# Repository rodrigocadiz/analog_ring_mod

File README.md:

# Analog ring modulation: a DIY approach inspired by historical techniques

## Overview

We present a device that implements a ring modulator intended to recreate historical analog audio. As simple as it sounds, the multiplication of two analog audio signals is not a straightforward task, mainly due to phenomena such as saturation or non-linearity. Drawing inspiration from historical realizations of ring modulation, we experimented with the most common methods described in the literature. Our device, which is comparatively inexpensive, improves upon the aforementioned alternatives from a DIY perspective. It is predominantly analog, adhering to the practices of the first decades of electroacoustic music, with the notable exception of the digital control for the sinusoidal carrier. We aim to strike a balance between analog audio technology and modern components and techniques. Additionally, this paper includes audio-visual demonstrations that showcase the practical uses of our ring modulator. A comprehensive GitHub repository provides open access to all the resources required for DIY enthusiasts to replicate our implementation.

## Authors
Tomas Koljatic, Michel Rozas, Cristián Garcés, Juan Parra Cancino, Rodrigo F. Cádiz

Pontificia Universidad Católica de Chile

Orpheus Instituut

## Demo videos 
Video 1:

Video 2: 

## Software Installation

The software for the Ring Modulator project is developed to be used with PlatformIO, an open source ecosystem for IoT development. To get started with PlatformIO, you can follow the installation guide here:

- [PlatformIO Installation Guide](https://docs.platformio.org/en/latest/core/installation.html)

Once PlatformIO is installed, you can clone this repository and open the firmware folder project within PlatformIO IDE.

## Hardware Design

The hardware for the Ring Modulator is developed using Autodesk Eagle. This provides a robust framework for designing printed circuit boards (PCBs) that are crucial for our project. You can find the hardware design files in the `hardware` directory of this repository.

For those new to Autodesk Eagle, you can learn more and get started with your designs here:

- [Autodesk Eagle](https://www.autodesk.com/products/eagle/overview)

## Acknowledgments/Contributing

The authors would like to thank Stockahusen Stiftung fur Musik for their support; María Julia Mancero for her participation as a piano performer in the videos; and the anonymous reviewers for their insightful comments and suggestions. This project was funded by the Office for the Arts and Culture of the Vice Presidency for Research, Pontificia Universidad Católica de Chile (ArTeCiH grant) and by ANID/Fondecyt 1230926 and ANID/Anillo ATE220041.

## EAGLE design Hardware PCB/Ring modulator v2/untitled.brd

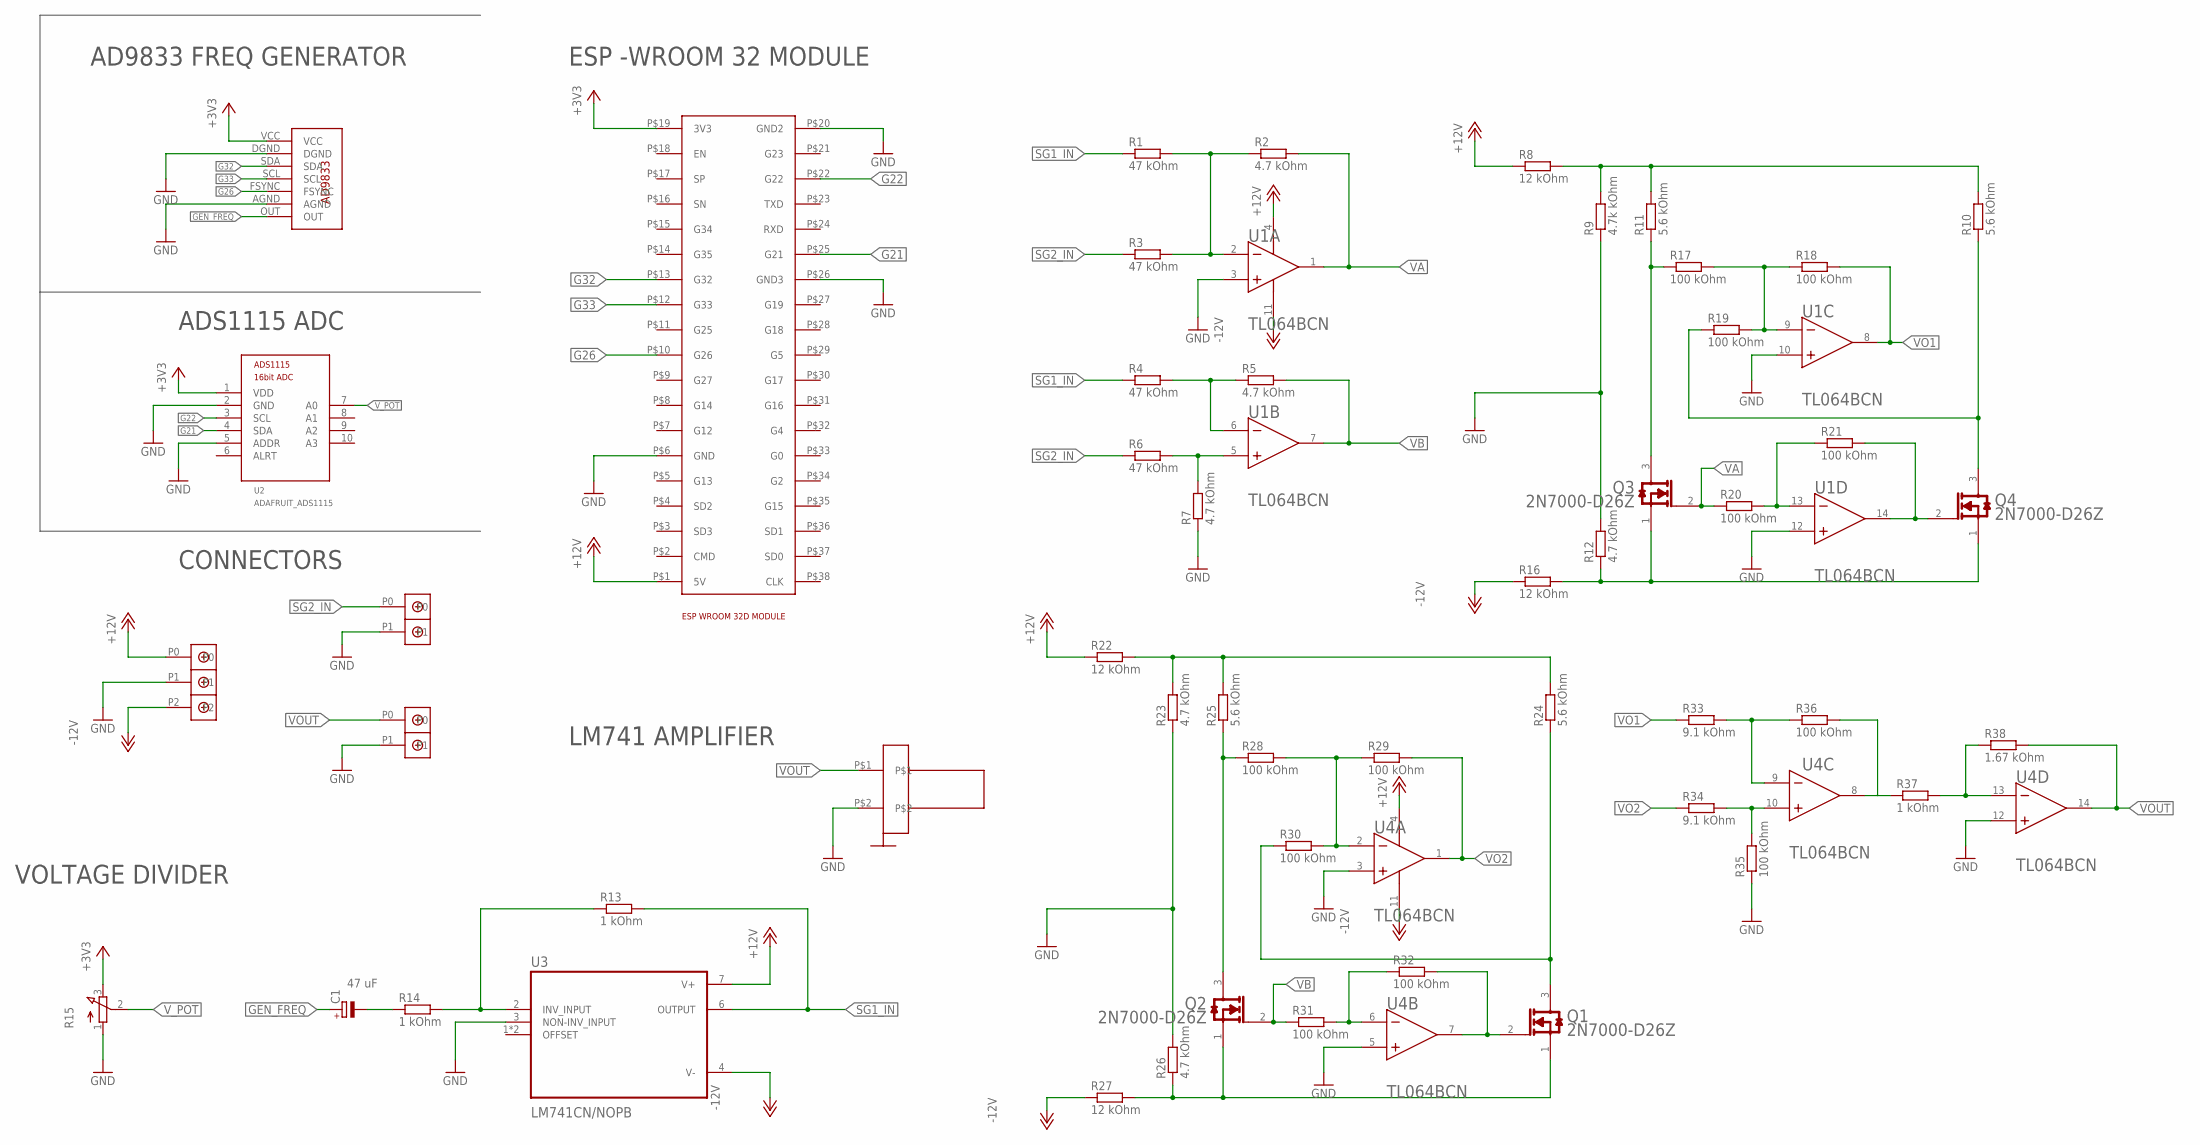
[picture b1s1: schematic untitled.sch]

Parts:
C1: 47 uF; E1,8-4
Q1, Q2, Q3, Q4: ON_SEMICONDUCTOR_2N7000-D26ZON_SEMICONDUCTOR_2N70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; ON_SEMICONDUCTOR_2N7000-D26Z_0
R1, R3, R4, R6: 47 kOhm; 0204/7
R2, R5, R7, R12, R23, R26: 4.7 kOhm; 0204/7
R8, R16, R22, R27: 12 kOhm; 0204/7
R9: 4.7k kOhm; 0204/7
R10, R11, R24, R25: 5.6 kOhm; 0204/7
R13, R14, R37: 1 kOhm; 0204/7
R15: 3RP/1610N
R17, R18, R19, R20, R21, R28, R29, R30, R31, R32, R35, R36: 100 kOhm; 0204/7
R33, R34: 9.1 kOhm; 0204/7
R38: 1.67 kOhm; 0204/7
U1, U4: TEXAS_INSTRUMENTS_TL064BCNTEXAS_INSTRUMENTS_TL064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; TEXAS_INSTRUMENTS_TL064BCN_0
U2: ADAFRUIT_ADS1115; ADAFRUIT_ADS1115_16BIT_I2C_ADC
U3: LM741CN/NOPB; DIP794W45P254L959H508Q8
U$1: ESP32
U$2: A9833; AD9833
U$3, U$5: DBCONN-1X2
U$4: DBCONN-1X3
U$6: FP

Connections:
+3V3: R15.3 (E), U2.1 (VDD), U$1.P$19 (3V3), U$2.VCC
+12V: R8.1, R22.1, U1.4 (VCC+), U3.7 (V+), U4.4 (VCC+), U$1.P$1 (5V), U$4.P0
-12V: R16.1, R27.1, U1.11 (VCC-), U3.4 (V-), U4.11 (VCC-), U$4.P2
G21: U2.4 (SDA), U$1.P$25 (G21)
G22: U2.3 (SCL), U$1.P$22 (G22)
G26: U$1.P$10 (G26), U$2.FSYNC
G32: U$1.P$13 (G32), U$2.SDA
G33: U$1.P$12 (G33), U$2.SCL
GEN_FREQ: C1.+, U$2.OUT
GND: R7.1, R9.1, R12.2, R15.1 (A), R23.1, R26.2, R35.1, U1.3 (IN1+), U1.10 (IN3+), U1.12 (IN4+), U2.2 (GND), U2.5 (ADDR), U3.3 (NON-INV_INPUT), U4.3 (IN1+), U4.5 (IN2+), U4.12 (IN4+), U$1.P$6 (GND), U$1.P$20 (GND2), U$1.P$26 (GND3), U$2.AGND, U$2.DGND, U$3.P1, U$4.P1, U$5.P1, U$6.P$2
unnamed: R1.2, R2.1, R3.2, U1.2 (IN1-)
unnamed: R4.2, R5.1, U1.6 (IN2-)
unnamed: R8.2, R9.2, R10.2, R11.2
unnamed: R13.1, R14.2, U3.2 (INV_INPUT)
unnamed: C1.-, R14.1
unnamed: R6.2, R7.2, U1.5 (IN2+)
unnamed: Q3.3 (D), R11.1, R17.1
unnamed: Q3.1 (S), Q4.1 (S), R12.1, R16.2
unnamed: Q4.3 (D), R10.1, R19.1
unnamed: R37.2, R38.1, U4.13 (IN4-)
unnamed: R20.2, R21.1, U1.13 (IN4-)
unnamed: R17.2, R18.1, R19.2, U1.9 (IN3-)
unnamed: Q4.2 (G), R21.2, U1.14 (OUT4)
unnamed: R22.2, R23.2, R24.2, R25.2
unnamed: Q1.1 (S), Q2.1 (S), R26.1, R27.2
unnamed: Q2.3 (D), R25.1, R28.1
unnamed: Q1.3 (D), R24.1, R30.1
unnamed: R28.2, R29.1, R30.2, U4.2 (IN1-)
unnamed: R33.2, R36.1, U4.9 (IN3-)
unnamed: R31.2, R32.1, U4.6 (IN2-)
unnamed: Q1.2 (G), R32.2, U4.7 (OUT2)
unnamed: R36.2, R37.1, U4.8 (OUT3)
unnamed: R34.2, R35.2, U4.10 (IN3+)
SG1_IN: R1.1, R4.1, R13.2, U3.6 (OUTPUT)
SG2_IN: R3.1, R6.1, U$3.P0
VA: Q3.2 (G), R2.2, R20.1, U1.1 (OUT1)
VB: Q2.2 (G), R5.2, R31.1, U1.7 (OUT2)
VO1: R18.2, R33.1, U1.8 (OUT3)
VO2: R29.2, R34.1, U4.1 (OUT1)
VOUT: R38.2, U4.14 (OUT4), U$5.P0, U$6.P$1
V_POT: R15.2 (S), U2.7 (A0)

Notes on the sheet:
ESP -WROOM 32 MODULE
AD9833 FREQ GENERATOR
ADS1115 ADC
CONNECTORS
LM741 AMPLIFIER
VOLTAGE DIVIDER

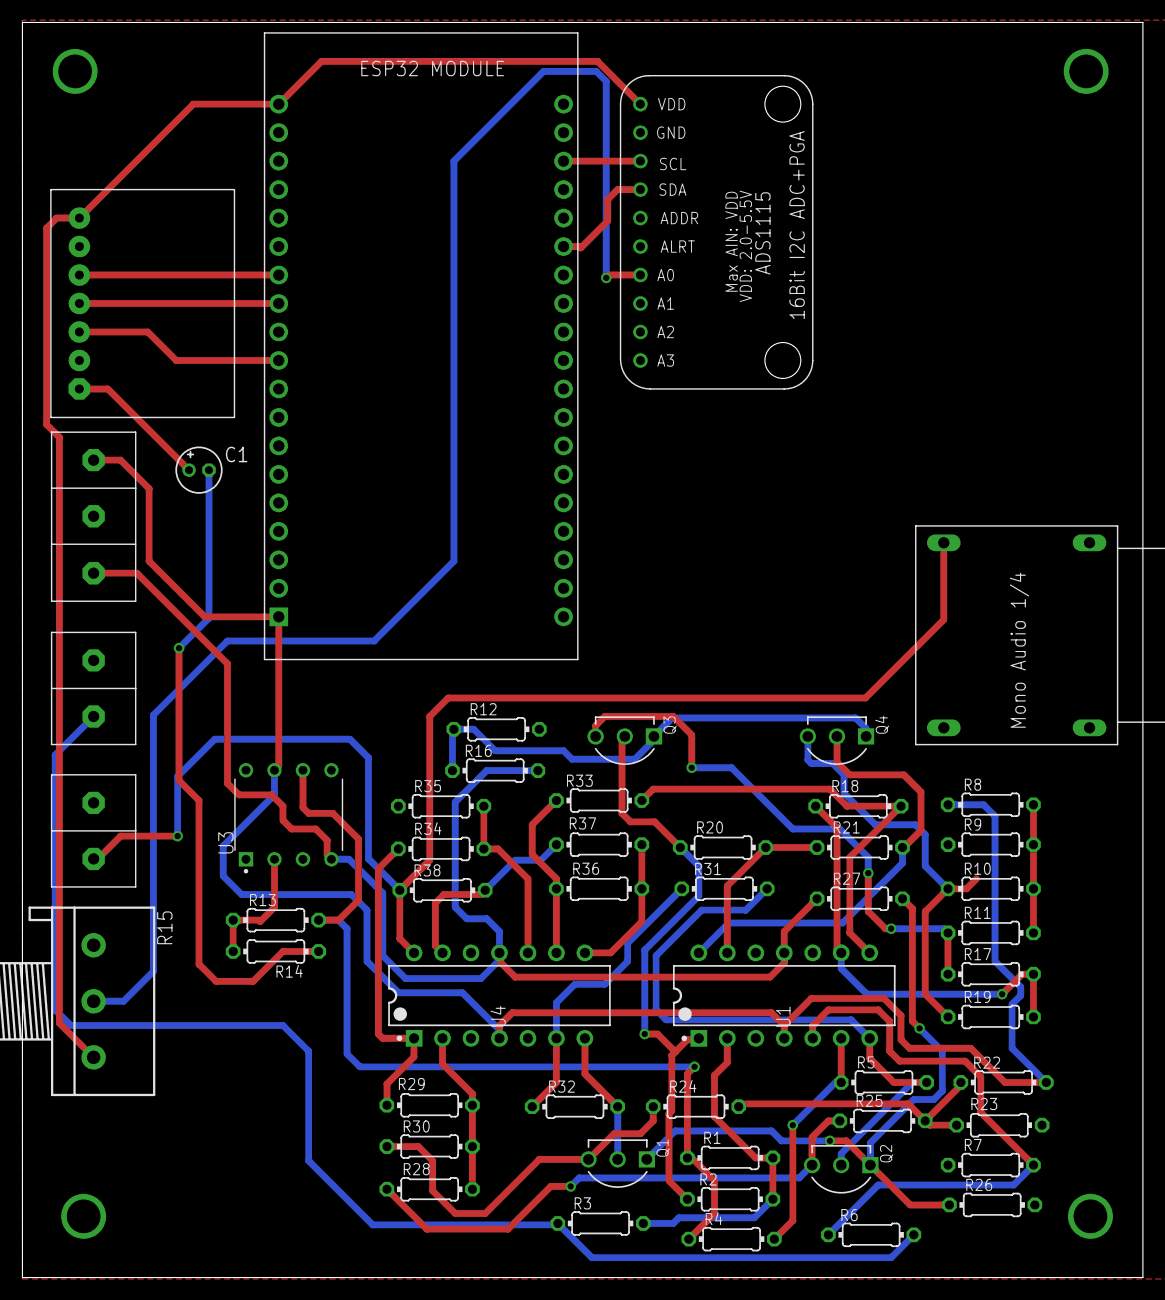
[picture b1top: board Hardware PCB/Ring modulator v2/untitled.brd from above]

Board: 2 copper layers, 99.9 x 111.9 mm, 53 parts (0 on the bottom side), 41 nets.

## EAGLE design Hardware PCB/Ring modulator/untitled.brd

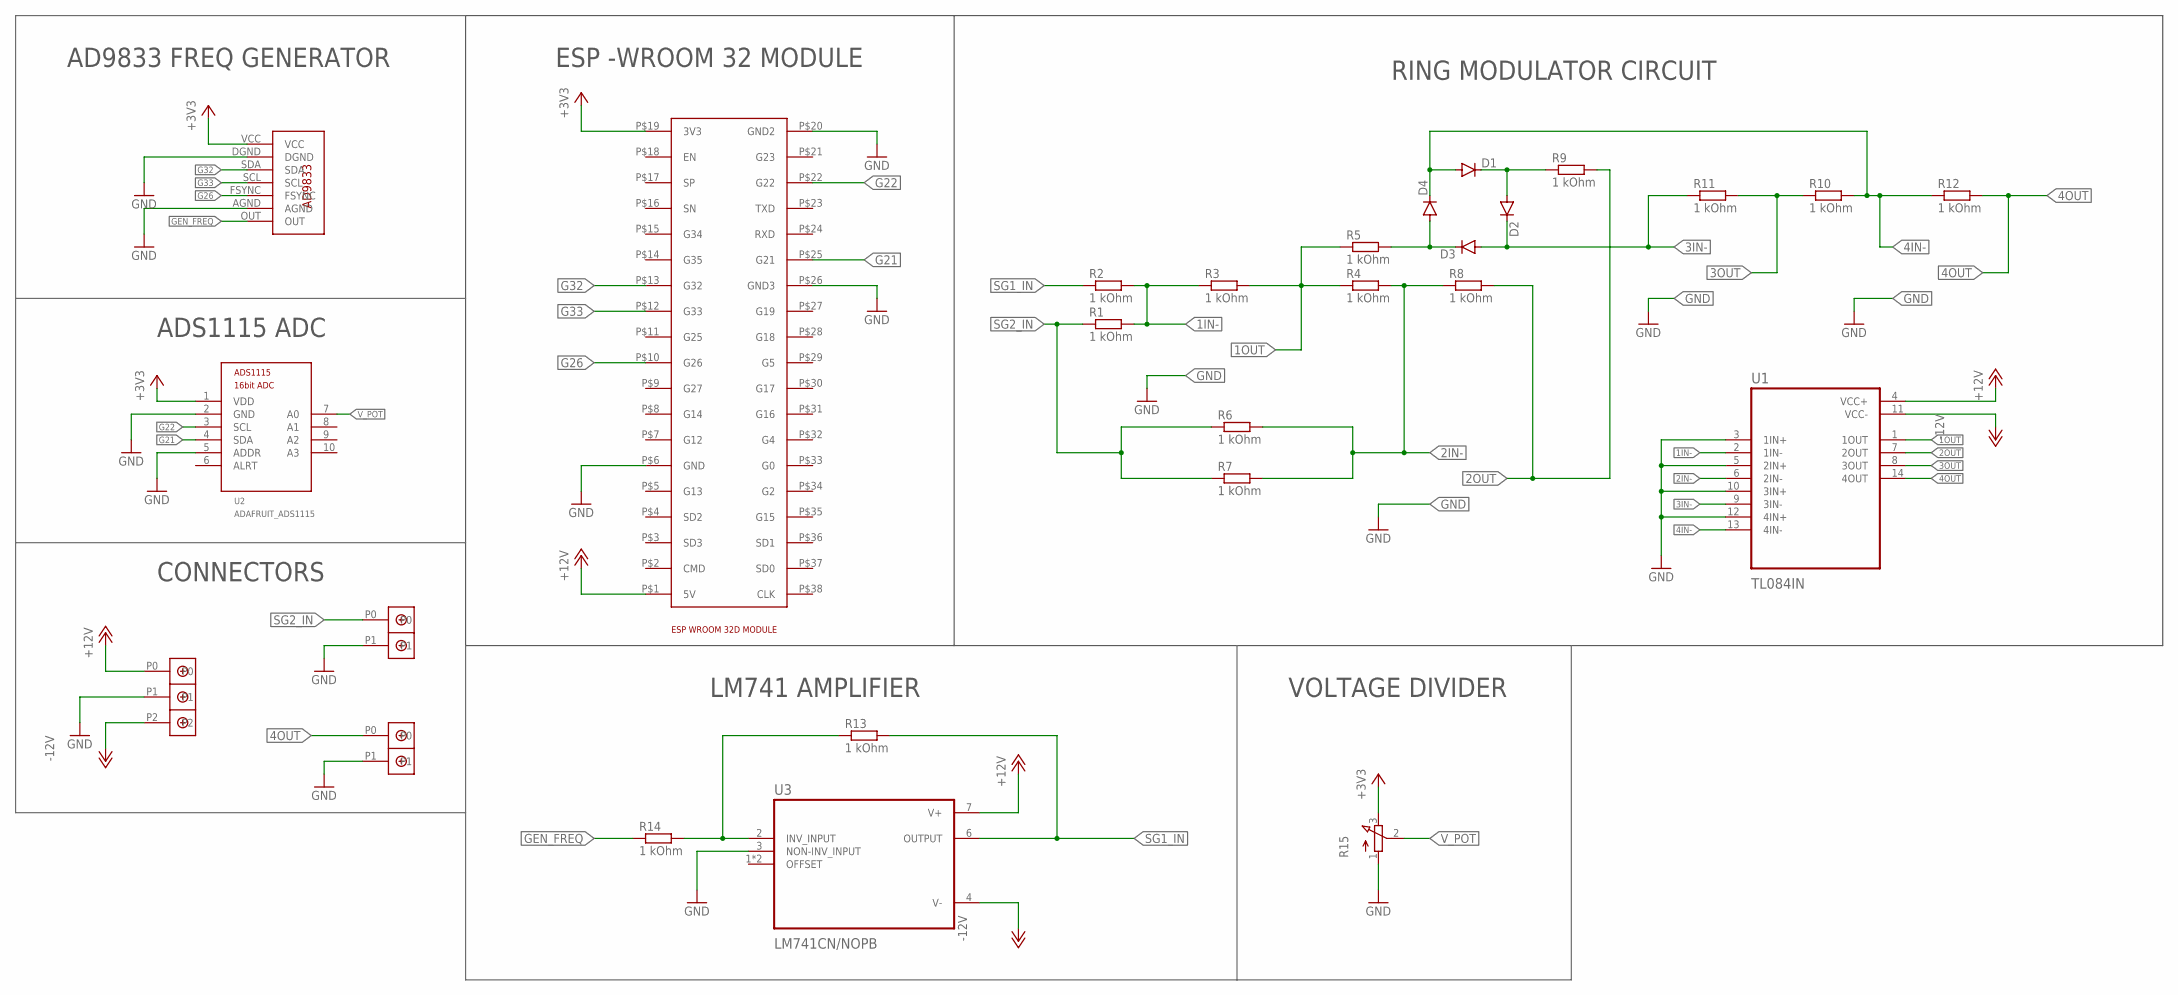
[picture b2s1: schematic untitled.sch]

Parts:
D1, D2, D3, D4: 1N4148DO35-7; DO35-7
R1, R2, R3, R4, R5, R6, R7, R8, R9, R10, R11, R12, R13, R14: 1 kOhm; 0204/7
R15: 3RP/1610N
U1: TL084IN; DIP794W45P254L1969H508Q14
U2: ADAFRUIT_ADS1115; ADAFRUIT_ADS1115_16BIT_I2C_ADC
U3: LM741CN/NOPB; DIP794W45P254L959H508Q8
U$1: ESP32
U$2: A9833; AD9833
U$3, U$5: DBCONN-1X2
U$4: DBCONN-1X3

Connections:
1IN-: R1.2, R2.2, R3.1, U1.2 (1IN-)
1OUT: R3.2, R4.1, R5.1, U1.1 (1OUT)
2IN-: R4.2, R6.2, R7.2, R8.1, U1.6 (2IN-)
2OUT: R8.2, R9.2, U1.7 (2OUT)
3IN-: D2.C, D3.A, R11.1, U1.9 (3IN-)
3OUT: R10.1, R11.2, U1.8 (3OUT)
4IN-: D1.A, D4.C, R10.2, R12.1, U1.13 (4IN-)
4OUT: R12.2, U1.14 (4OUT), U$5.P0
+3V3: R15.3 (E), U2.1 (VDD), U$1.P$19 (3V3), U$2.VCC
+12V: U1.4 (VCC+), U3.7 (V+), U$1.P$1 (5V), U$4.P0
-12V: U1.11 (VCC-), U3.4 (V-), U$4.P2
G21: U2.4 (SDA), U$1.P$25 (G21)
G22: U2.3 (SCL), U$1.P$22 (G22)
G26: U$1.P$10 (G26), U$2.FSYNC
G32: U$1.P$13 (G32), U$2.SDA
G33: U$1.P$12 (G33), U$2.SCL
GEN_FREQ: R14.1, U$2.OUT
GND: R15.1 (A), U1.3 (1IN+), U1.5 (2IN+), U1.10 (3IN+), U1.12 (4IN+), U2.2 (GND), U2.5 (ADDR), U3.3 (NON-INV_INPUT), U$1.P$6 (GND), U$1.P$20 (GND2), U$1.P$26 (GND3), U$2.AGND, U$2.DGND, U$3.P1, U$4.P1, U$5.P1
unnamed: D3.C, D4.A, R5.2
unnamed: D1.C, D2.A, R9.1
unnamed: R13.1, R14.2, U3.2 (INV_INPUT)
SG1_IN: R2.1, R13.2, U3.6 (OUTPUT)
SG2_IN: R1.1, R6.1, R7.1, U$3.P0
V_POT: R15.2 (S), U2.7 (A0)

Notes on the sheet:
RING MODULATOR CIRCUIT
ESP -WROOM 32 MODULE
AD9833 FREQ GENERATOR
ADS1115 ADC
CONNECTORS
LM741 AMPLIFIER
VOLTAGE DIVIDER

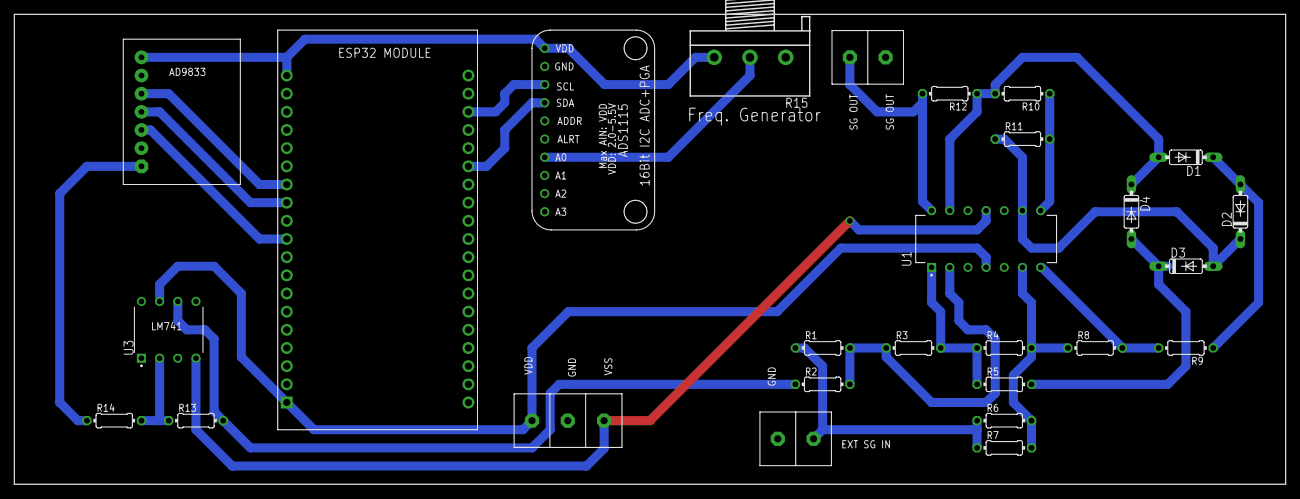
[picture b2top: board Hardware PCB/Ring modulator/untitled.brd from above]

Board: 2 copper layers, 177.8 x 65.7 mm, 27 parts (0 on the bottom side), 24 nets.

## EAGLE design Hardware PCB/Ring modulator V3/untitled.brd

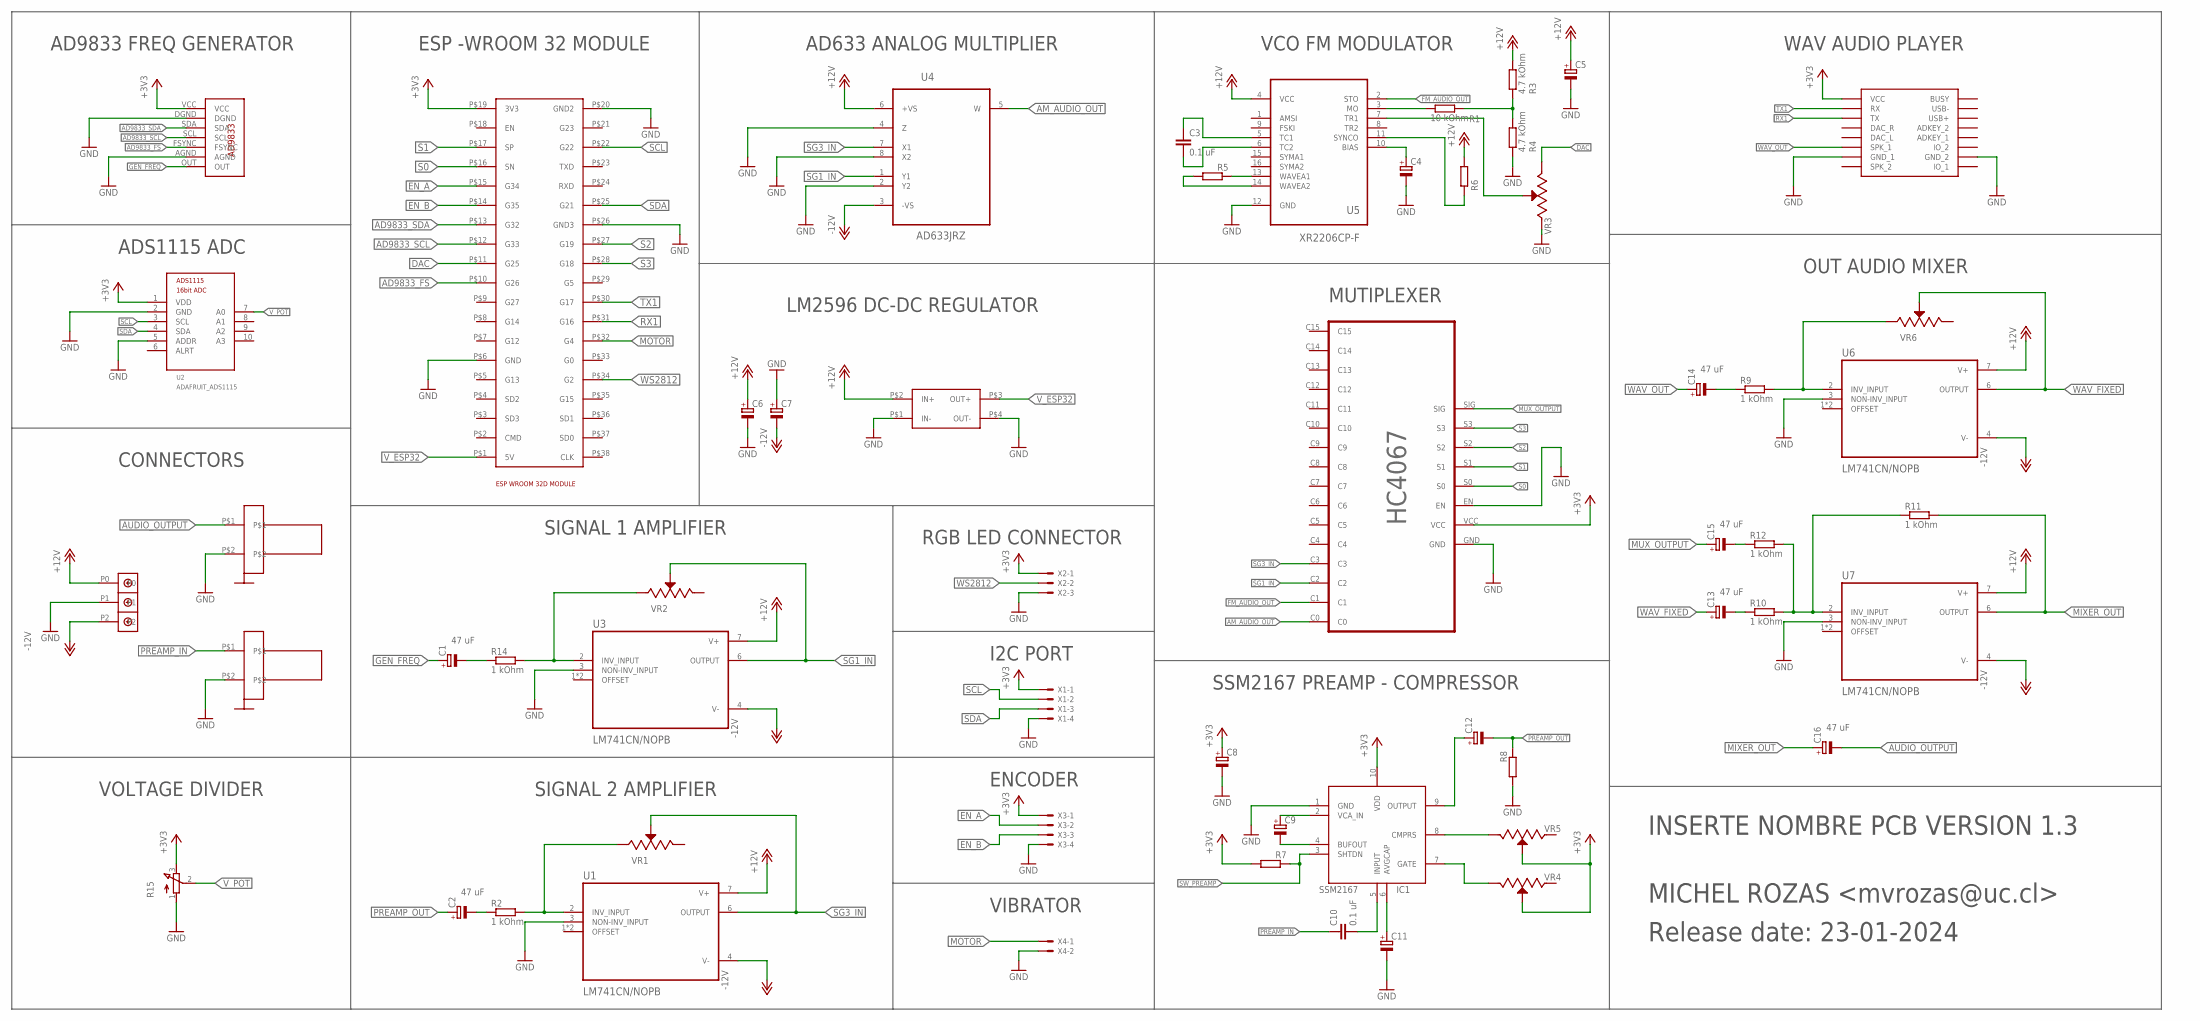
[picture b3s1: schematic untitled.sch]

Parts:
C1, C2, C13, C14, C15, C16: 47 uF; E1,8-4
C3, C10: 0.1 uF; C050-030X075
C4, C5: 1 uF; E1,8-4
C6, C7: 100 uF; E1,8-4
C8, C9, C11, C12: 10 uF; E1,8-4
IC1: SSM2167; MSOP10
R1, R6: 10 kOhm; 0204/7
R2, R9, R10, R11, R12, R14: 1 kOhm; 0204/7
R3, R4: 4.7 kOhm; 0204/7
R5: 200 Ohm; 0204/7
R7: 500 kOhm; 0204/7
R8: 100 kOhm; 0204/7
R15: 3RP/1610N
U1, U3, U6, U7: LM741CN/NOPB; DIP794W45P254L959H508Q8
U2: ADAFRUIT_ADS1115; ADAFRUIT_ADS1115_16BIT_I2C_ADC
U4: AD633JRZ; SOIC127P600X175-8N
U5: XR2206CP-F; DIP254P762X533-16
U$1: ESP32
U$2: A9833; AD9833
U$3: LM2596
U$4: DBCONN-1X3
U$5: HC4067_BREAKOUT_BOARD; ANALOG_MUX_BREAKOUT_HC4067
U$6, U$7: FP
U$8: DFPLAYER
VR1, VR2, VR3, VR4, VR5, VR6: 3296W-1-104LF; TRIM_3296W-1-104LF
X1, X3: JST-XH-04-PIN-ROUND-PAD; JST-XH-04-PACKAGE-ROUND-PAD
X2: JST-XH-03-PIN-ROUND-PAD; JST-XH-03-PACKAGE-ROUND-PAD
X4: JST-XH-02-PIN-ROUND-PAD; JST-XH-02-PACKAGE-ROUND-PAD

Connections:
+3V3: C8.+, IC1.10 (VDD), R7.1, R15.3 (E), U2.1 (VDD), U$1.P$19 (3V3), U$2.VCC, U$5.VCC, U$8.VCC, VR4.2 (WIPER), VR5.2 (WIPER), X1.1, X2.1, X3.1
+12V: C5.+, C6.+, R3.2, R6.2, U1.7 (V+), U3.7 (V+), U4.6 (+VS), U5.4 (VCC), U6.7 (V+), U7.7 (V+), U$3.P$2 (IN+), U$4.P0
-12V: C7.-, U1.4 (V-), U3.4 (V-), U4.3 (-VS), U6.4 (V-), U7.4 (V-), U$4.P2
AD9833_FS: U$1.P$10 (G26), U$2.FSYNC
AD9833_SCL: U$1.P$12 (G33), U$2.SCL
AD9833_SDA: U$1.P$13 (G32), U$2.SDA
AM_AUDIO_OUT: U4.5 (W), U$5.C0
AUDIO_OUTPUT: C16.-, U$6.P$1
DAC: U$1.P$11 (G25), VR3.3 (CW)
EN_A: U$1.P$15 (G34), X3.2
EN_B: U$1.P$14 (G35), X3.3
FM_AUDIO_OUT: U5.2 (STO), U$5.C1
GEN_FREQ: C1.+, U$2.OUT
GND: C4.-, C5.-, C6.-, C7.+, C8.-, C11.-, IC1.1 (GND), R4.1, R8.1, R15.1 (A), U1.3 (NON-INV_INPUT), U2.2 (GND), U2.5 (ADDR), U3.3 (NON-INV_INPUT), U4.2 (Y2), U4.4 (Z), U4.8 (X2), U5.12 (GND), U6.3 (NON-INV_INPUT), U7.3 (NON-INV_INPUT), U$1.P$6 (GND), U$1.P$20 (GND2), U$1.P$26 (GND3), U$2.AGND, U$2.DGND, U$3.P$1 (IN-), U$4.P1, U$5.EN, U$6.P$2, U$7.P$2, U$8.GND_1, U$8.GND_2, VR3.1 (CCW), X1.4, X2.3, X3.4, X4.2
MIXER_OUT: C16.+, R11.2, U7.6 (OUTPUT)
MOTOR: U$1.P$32 (G4), X4.1
MUX_OUTPUT: C15.+, U$5.SIG
unnamed: R2.2, U1.2 (INV_INPUT), VR1.1 (CCW)
unnamed: C2.-, R2.1
unnamed: R1.1, U5.3 (MO)
unnamed: R14.2, U3.2 (INV_INPUT), VR2.1 (CCW)
unnamed: C1.-, R14.1
unnamed: R1.2, R3.1, R4.2
unnamed: C3.1, U5.5 (TC1)
unnamed: C3.2, U5.6 (TC2)
unnamed: U5.7 (TR1), VR3.2 (WIPER)
unnamed: R5.2, U5.13 (WAVEA1)
unnamed: R5.1, U5.14 (WAVEA2)
unnamed: R6.1, U5.11 (SYNCO)
unnamed: C4.+, U5.10 (BIAS)
unnamed: C10.2, IC1.5 (INPUT)
unnamed: C9.+, IC1.2 (VCA_IN)
unnamed: C9.-, IC1.4 (BUFOUT)
unnamed: C11.+, IC1.6 (AVGCAP)
unnamed: IC1.8 (CMPRS), VR5.3 (CW)
unnamed: IC1.7 (GATE), VR4.3 (CW)
unnamed: C12.+, IC1.9 (OUTPUT)
unnamed: R9.2, U6.2 (INV_INPUT), VR6.1 (CCW)
unnamed: C14.-, R9.1
unnamed: R10.2, R11.1, R12.2, U7.2 (INV_INPUT)
unnamed: C13.-, R10.1
unnamed: C15.-, R12.1
PREAMP_IN: C10.1, U$7.P$1
PREAMP_OUT: C2.+, C12.-, R8.2
RX1: U$1.P$31 (G16), U$8.TX
S0: U$1.P$16 (SN), U$5.S0
S1: U$1.P$17 (SP), U$5.S1
S2: U$1.P$27 (G19), U$5.S2
S3: U$1.P$28 (G18), U$5.S3
SCL: U2.3 (SCL), U$1.P$22 (G22), X1.2
SDA: U2.4 (SDA), U$1.P$25 (G21), X1.3
SG1_IN: U3.6 (OUTPUT), U4.1 (Y1), U$5.C2, VR2.2 (WIPER)
SG3_IN: U1.6 (OUTPUT), U4.7 (X1), U$5.C3, VR1.2 (WIPER)
SW_PREAMP: IC1.3 (SHTDN), R7.2
TX1: U$1.P$30 (G17), U$8.RX
V_ESP32: U$1.P$1 (5V), U$3.P$3 (OUT+)
V_POT: R15.2 (S), U2.7 (A0)
WAV_FIXED: C13.+, U6.6 (OUTPUT), VR6.2 (WIPER)
WAV_OUT: C14.+, U$8.SPK1 (SPK_1)
WS2812: U$1.P$34 (G2), X2.2

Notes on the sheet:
ESP -WROOM 32 MODULE
AD9833 FREQ GENERATOR
ADS1115 ADC
CONNECTORS
SIGNAL 1 AMPLIFIER
VOLTAGE DIVIDER
SIGNAL 2 AMPLIFIER
AD633 ANALOG MULTIPLIER
LM2596 DC-DC REGULATOR
RGB LED CONNECTOR
I2C PORT
ENCODER
VIBRATOR
VCO FM MODULATOR
MUTIPLEXER
SSM2167 PREAMP - COMPRESSOR
WAV AUDIO PLAYER
OUT AUDIO MIXER
INSERTE NOMBRE PCB VERSION 1.3
MICHEL ROZAS <mvrozas@uc.cl>
Release date: 23-01-2024

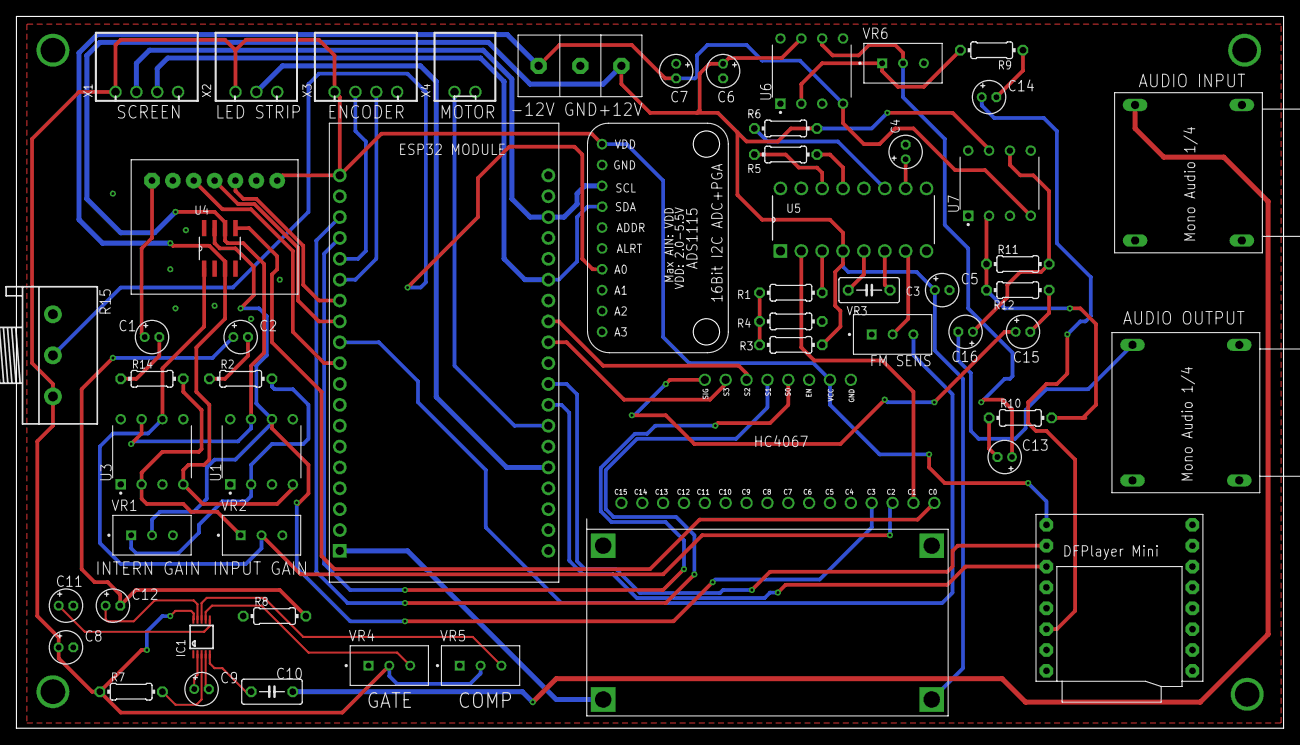
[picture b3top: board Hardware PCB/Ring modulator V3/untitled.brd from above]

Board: 2 copper layers, 154.3 x 86.7 mm, 56 parts (0 on the bottom side), 60 nets.
